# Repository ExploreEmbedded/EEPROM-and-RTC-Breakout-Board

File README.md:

# EEPROM-and-RTC-Breakout-Board

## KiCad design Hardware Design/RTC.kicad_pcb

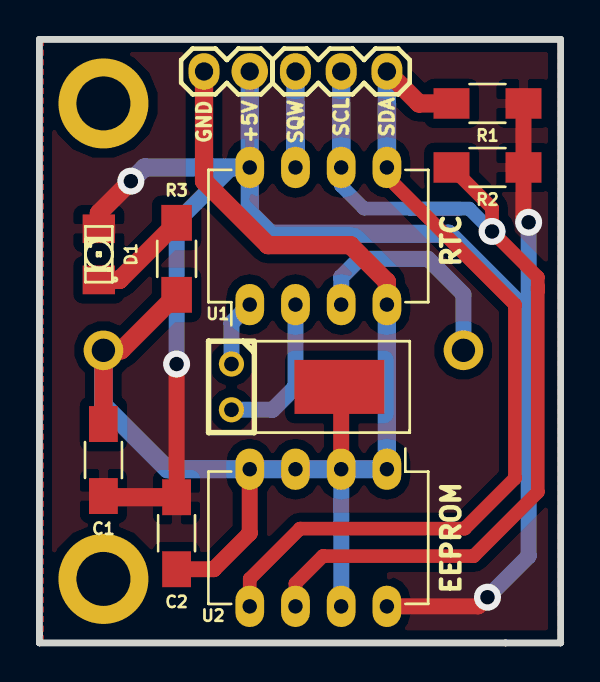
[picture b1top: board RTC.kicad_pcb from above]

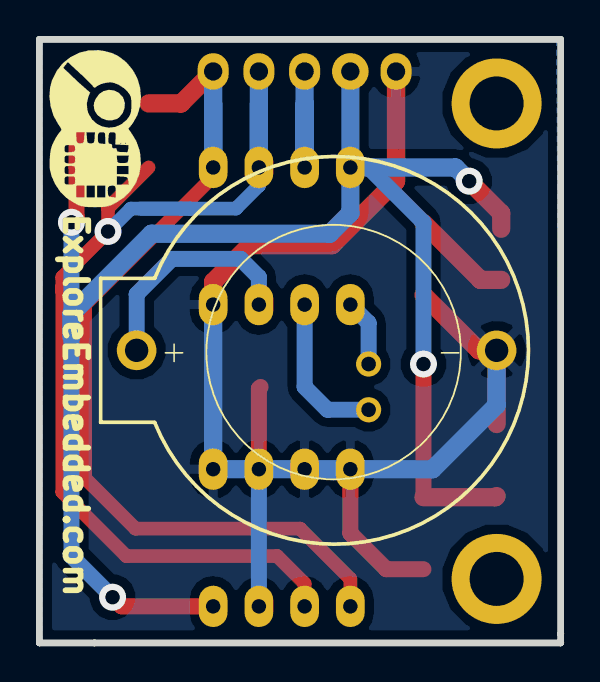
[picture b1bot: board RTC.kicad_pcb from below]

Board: 2 copper layers, 29.0 x 33.5 mm, 15 parts (2 on the bottom side), 9 nets.

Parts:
3,3V1: BATTERY; RTC_Battery_Holder
C1: 0.1uF; C_1206_HandSoldering
C2: 1uF; C_1206_HandSoldering
D1: LED; LED-1206_NEW
K1: I2C; Pin_Header_Straight_1x03
P1: PWR; Pin_Header_Straight_1x02
P2: CONN_01X01; Logo_8
P3, P5: CONN_01X01; M3_mounting
R1, R2: 10k; R_1206_HandSoldering
R3: 470r; R_1206_HandSoldering
U1: DS1307; DIP-8_W7.62mm_LongPads
U2: 24C16; DIP-8_W7.62mm_LongPads
X1: CRYSTAL_SMD; RTC_Crystal_1

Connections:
/SCL: K1.2, R2.2, U1.6, U2.6
/SDA: K1.3, R1.2, U1.5, U2.5
GND: 3,3V1.2, C1.2, C2.2, P1.1, R3.2, U1.4, U2.1, U2.2, U2.3, U2.4, U2.7, X1.3
unnamed: 3,3V1.1, U1.3
unnamed: D1.2, R3.1
unnamed: K1.1, U1.7
unnamed: U1.1, X1.1
unnamed: U1.2, X1.2
VCC: C1.1, C2.1, D1.1, P1.2, R1.1, R2.1, U1.8, U2.8

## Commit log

2016-09-14 Added Design Files
2016-09-14 Added pdf
